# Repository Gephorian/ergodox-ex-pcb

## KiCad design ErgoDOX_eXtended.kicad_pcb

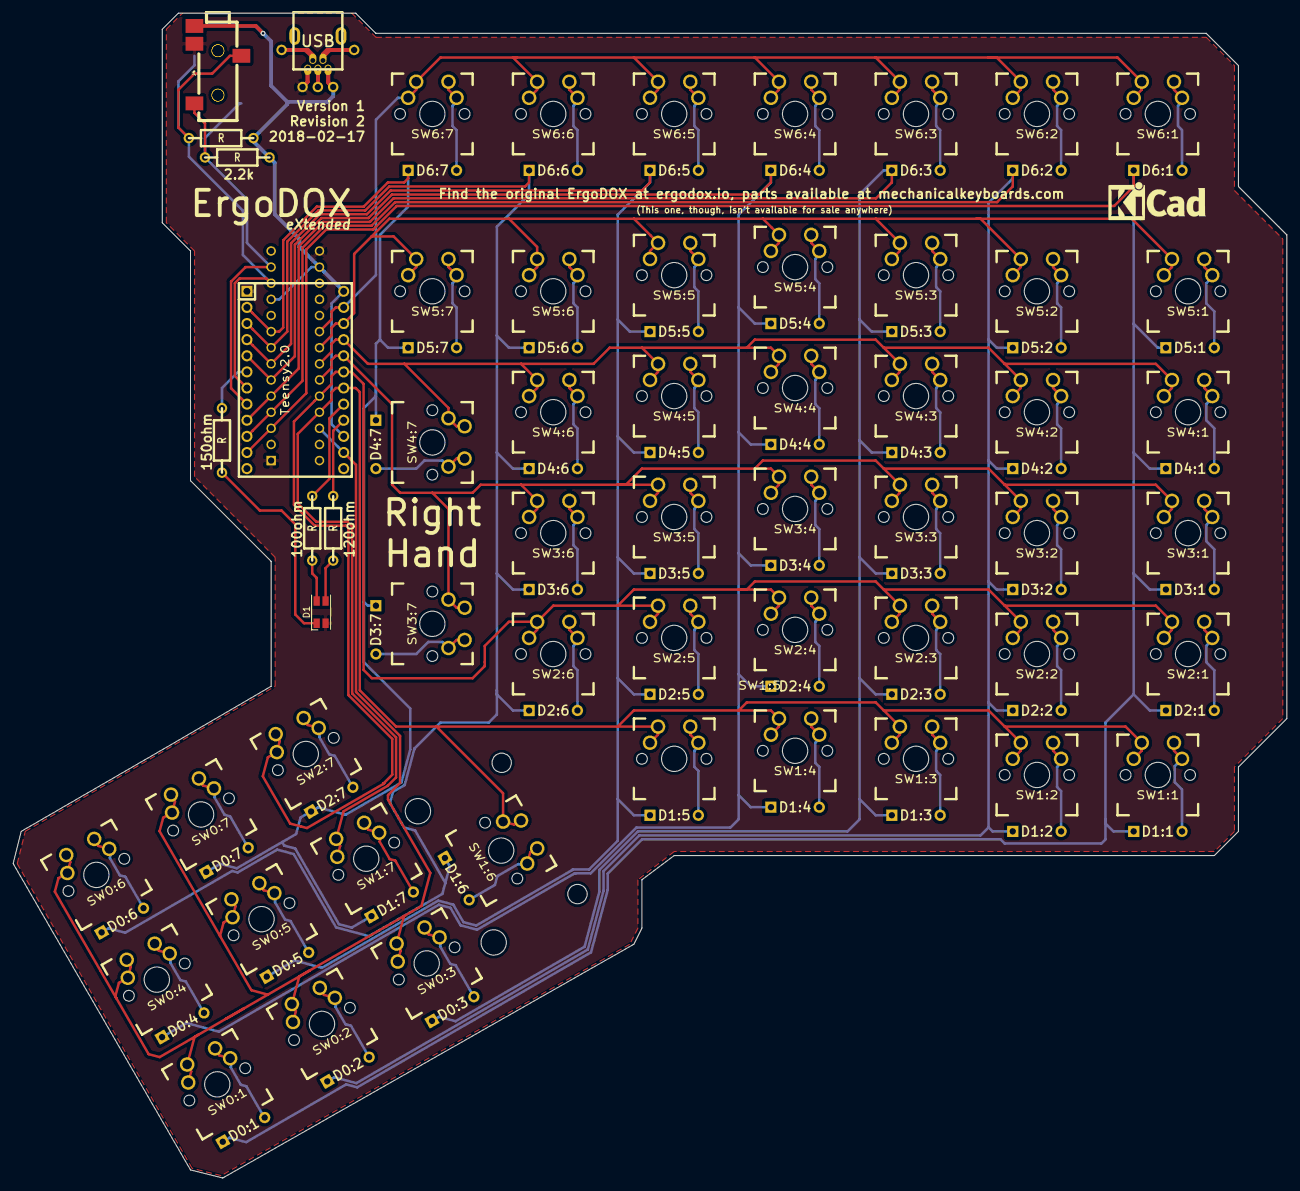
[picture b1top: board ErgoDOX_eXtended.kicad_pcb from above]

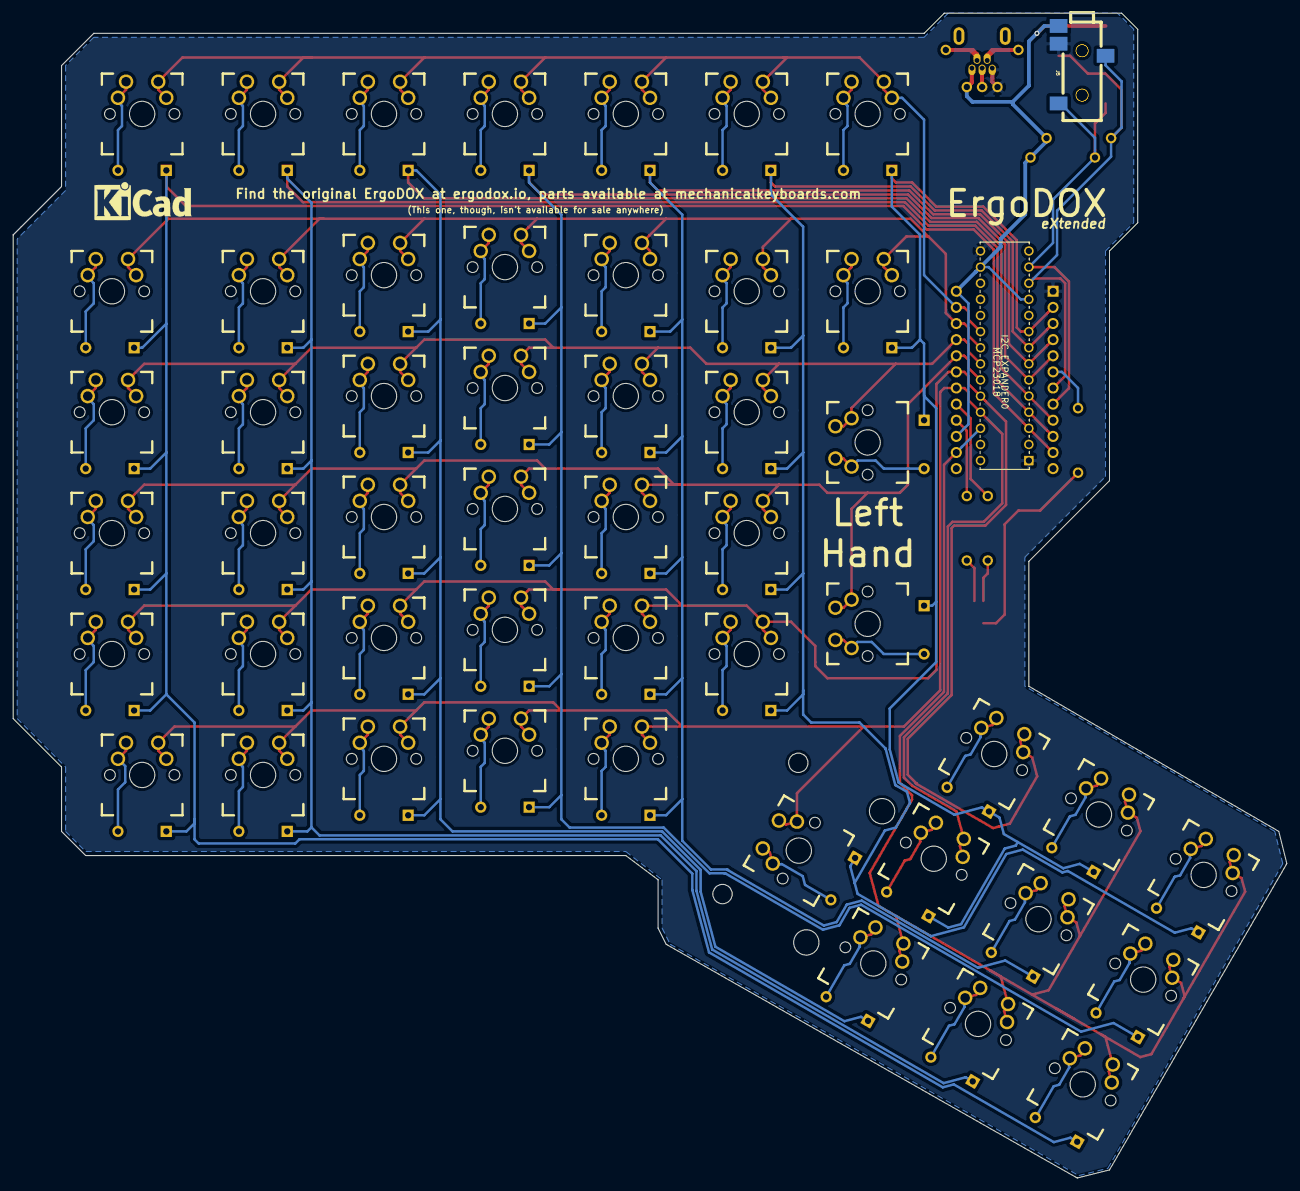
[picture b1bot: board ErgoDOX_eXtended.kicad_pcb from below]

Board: 2 copper layers, 200.7 x 183.5 mm, 109 parts (2 on the bottom side), 73 nets.

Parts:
D0:1, D0:2, D0:3, D0:4, D0:5, D0:6, D0:7, D1:1, D1:2, D1:3, D1:4, D1:5, D1:6, D1:7, D2:1, D2:2, D2:3, D2:4, D2:5, D2:6, D2:7, D3:1, D3:2, D3:3, D3:4, D3:5, D3:6, D3:7, D4:1, D4:2, D4:3, D4:4, D4:5, D4:6, D4:7, D5:1, D5:2, D5:3, D5:4, D5:5, D5:6, D5:7, D6:1, D6:2, D6:3, D6:4, D6:5, D6:6, D6:7: DIODE; CHERRY_MX_DIODE
D1: LED_RCBG; LED_RGB_1210
I2C_EXPANDER0: MCP23018
J4, J5: 4PIN; SJ-43514-SMT
R1, R2, R3, R4, R5: R; RESISTOR
SW0:1, SW0:2, SW0:3, SW0:4, SW0:5, SW0:6, SW0:7, SW1:1, SW1:2, SW1:3, SW1:4, SW1:5, SW1:7, SW2:2, SW2:3, SW2:4, SW2:5, SW2:6, SW2:7, SW3:2, SW3:3, SW3:4, SW3:5, SW3:6, SW4:2, SW4:3, SW4:4, SW4:5, SW4:6, SW5:2, SW5:3, SW5:4, SW5:5, SW5:6, SW5:7, SW6:1, SW6:2, SW6:3, SW6:4, SW6:5, SW6:6, SW6:7: SWITCH; CHERRY_PCB_100H
SW1:6: SWITCH; CHERRY_PCB_200H
SW2:1, SW3:1, SW3:7, SW4:1, SW4:7, SW5:1: SWITCH; CHERRY_PCB_150H
Teensy2.0: Teensy2.0; TEENSY_2.0
USB1: USB; USBMINImod

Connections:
Col0: D0:1.2, D1:1.2, D2:1.2, D3:1.2, D4:1.2, D5:1.2, D6:1.2, I2C_EXPANDER0.3, Teensy2.0.11
Col1: D0:2.2, D1:2.2, D2:2.2, D3:2.2, D4:2.2, D5:2.2, D6:2.2, I2C_EXPANDER0.4, Teensy2.0.10
Col2: D0:3.2, D1:3.2, D2:3.2, D3:3.2, D4:3.2, D5:3.2, D6:3.2, I2C_EXPANDER0.5, Teensy2.0.9
Col3: D0:4.2, D1:4.2, D2:4.2, D3:4.2, D4:4.2, D5:4.2, D6:4.2, I2C_EXPANDER0.6, Teensy2.0.5
Col4: D0:5.2, D1:5.2, D2:5.2, D3:5.2, D4:5.2, D5:5.2, D6:5.2, I2C_EXPANDER0.7, Teensy2.0.4
Col5: D0:6.2, D1:6.2, D2:6.2, D3:6.2, D4:6.2, D5:6.2, D6:6.2, I2C_EXPANDER0.8, Teensy2.0.3
Col6: D0:7.2, D1:7.2, D2:7.2, D3:7.2, D4:7.2, D5:7.2, D6:7.2, I2C_EXPANDER0.9, Teensy2.0.2
GND: D1.2, I2C_EXPANDER0.1, I2C_EXPANDER0.15, J4.4, J5.4, Teensy2.0.1, USB1.5
LED_B: D1.3, R5.1
LED_G: D1.4, R4.1
LED_PIN_B: R5.2, Teensy2.0.21
LED_PIN_G: R4.2, Teensy2.0.22
LED_PIN_R: R3.2, Teensy2.0.6
LED_R: D1.1, R3.1
unnamed: D0:1.1, SW0:1.2
unnamed: D0:2.1, SW0:2.2
unnamed: D0:3.1, SW0:3.2
unnamed: D0:4.1, SW0:4.2
unnamed: D0:5.1, SW0:5.2
unnamed: D0:6.1, SW0:6.2
unnamed: D0:7.1, SW0:7.2
unnamed: D1:1.1, SW1:1.2
unnamed: D1:2.1, SW1:2.2
unnamed: D1:3.1, SW1:3.2
unnamed: D1:4.1, SW1:4.2
unnamed: D1:5.1, SW1:5.2
unnamed: D1:6.1, SW1:6.2
unnamed: D1:7.1, SW1:7.2
unnamed: D2:1.1, SW2:1.2
unnamed: D2:2.1, SW2:2.2
unnamed: D2:3.1, SW2:3.2
unnamed: D2:4.1, SW2:4.2
unnamed: D2:5.1, SW2:5.2
unnamed: D2:6.1, SW2:6.2
unnamed: D2:7.1, SW2:7.2
unnamed: D3:1.1, SW3:1.2
unnamed: D3:2.1, SW3:2.2
unnamed: D3:3.1, SW3:3.2
unnamed: D3:4.1, SW3:4.2
unnamed: D3:5.1, SW3:5.2
unnamed: D3:6.1, SW3:6.2
unnamed: D3:7.1, SW3:7.2
unnamed: D4:1.1, SW4:1.2
unnamed: D4:2.1, SW4:2.2
unnamed: D4:3.1, SW4:3.2
unnamed: D4:4.1, SW4:4.2
unnamed: D4:5.1, SW4:5.2
unnamed: D4:6.1, SW4:6.2
unnamed: D4:7.1, SW4:7.2
unnamed: D5:1.1, SW5:1.2
unnamed: D5:2.1, SW5:2.2
unnamed: D5:3.1, SW5:3.2
unnamed: D5:4.1, SW5:4.2
unnamed: D5:5.1, SW5:5.2
unnamed: D5:6.1, SW5:6.2
unnamed: D5:7.1, SW5:7.2
unnamed: D6:1.1, SW6:1.2
unnamed: D6:2.1, SW6:2.2
unnamed: D6:3.1, SW6:3.2
unnamed: D6:4.1, SW6:4.2
unnamed: D6:5.1, SW6:5.2
unnamed: D6:6.1, SW6:6.2
unnamed: D6:7.1, SW6:7.2
Row0: I2C_EXPANDER0.26, SW0:1.1, SW0:2.1, SW0:3.1, SW0:4.1, SW0:5.1, SW0:6.1, SW0:7.1, Teensy2.0.19
Row1: I2C_EXPANDER0.25, SW1:1.1, SW1:2.1, SW1:3.1, SW1:4.1, SW1:5.1, SW1:6.1, SW1:7.1, Teensy2.0.23
Row2: I2C_EXPANDER0.24, SW2:1.1, SW2:2.1, SW2:3.1, SW2:4.1, SW2:5.1, SW2:6.1, SW2:7.1, Teensy2.0.24
Row3: I2C_EXPANDER0.23, SW3:1.1, SW3:2.1, SW3:3.1, SW3:4.1, SW3:5.1, SW3:6.1, SW3:7.1, Teensy2.0.25
Row4: I2C_EXPANDER0.22, SW4:1.1, SW4:2.1, SW4:3.1, SW4:4.1, SW4:5.1, SW4:6.1, SW4:7.1, Teensy2.0.26
Row5: I2C_EXPANDER0.21, SW5:1.1, SW5:2.1, SW5:3.1, SW5:4.1, SW5:5.1, SW5:6.1, SW5:7.1, Teensy2.0.27
Row6: I2C_EXPANDER0.20, SW6:1.1, SW6:2.1, SW6:3.1, SW6:4.1, SW6:5.1, SW6:6.1, SW6:7.1, Teensy2.0.28
SCL: I2C_EXPANDER0.12, J4.3, J5.3, R1.1, Teensy2.0.7
SDA: I2C_EXPANDER0.13, J4.2, J5.2, R2.2, Teensy2.0.8
VCC: I2C_EXPANDER0.11, I2C_EXPANDER0.16, J4.1, J5.1, R1.2, R2.1, Teensy2.0.20, Teensy2.0.29, USB1.1

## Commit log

2018-03-08 Initial commit
    Sorry it's a mess, I'll clean it up eventually

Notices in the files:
parts and their libraries:
Copyright 2016 Accelerated Designs. All rights reserved.
